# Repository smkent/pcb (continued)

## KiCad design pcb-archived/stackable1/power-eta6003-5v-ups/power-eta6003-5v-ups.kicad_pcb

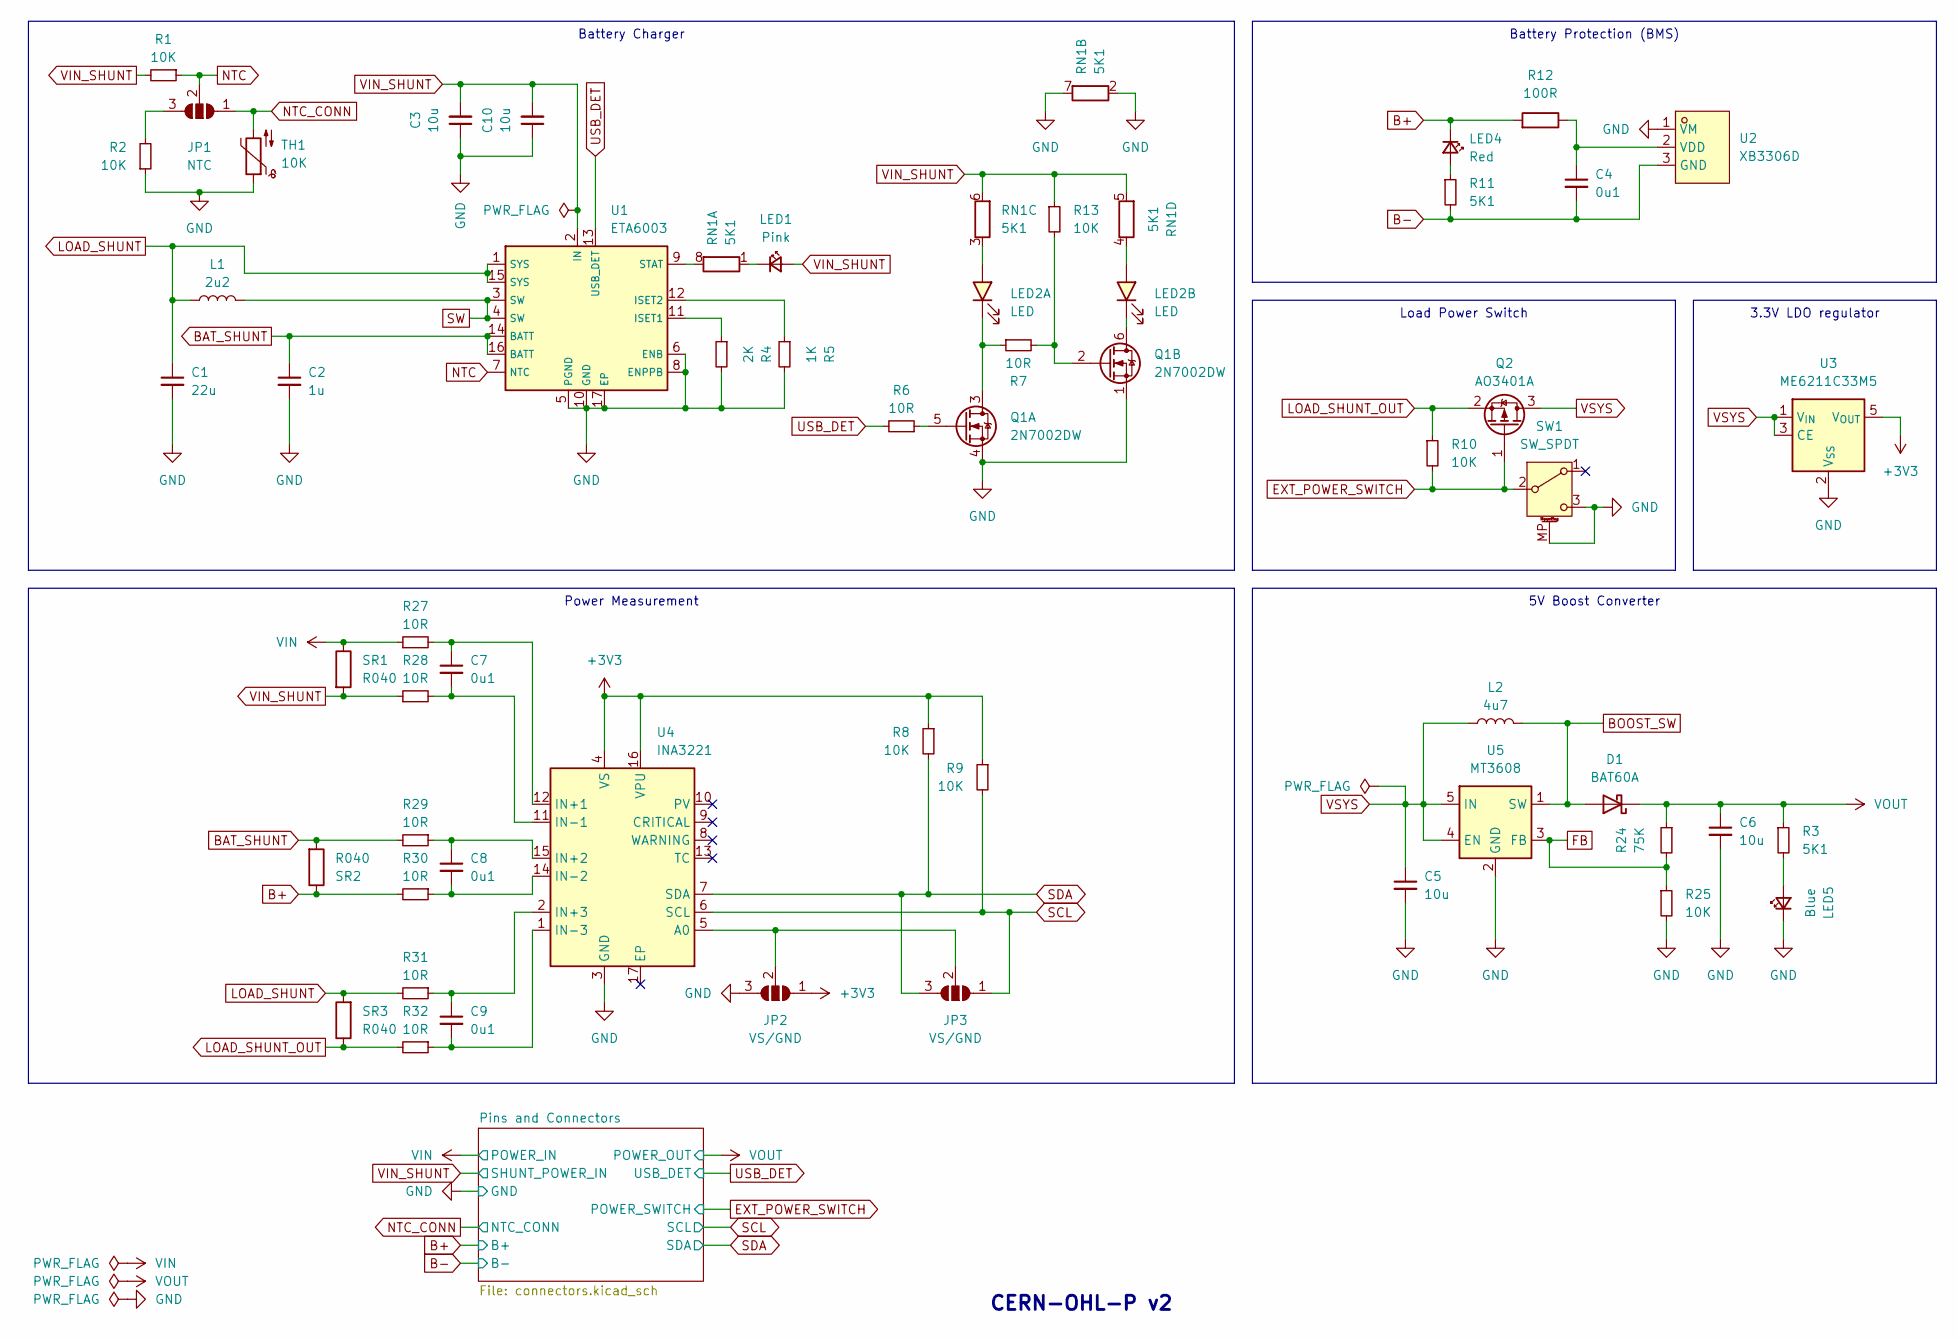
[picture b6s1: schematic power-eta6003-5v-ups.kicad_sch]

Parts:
C1: 22u; C_0805_2012Metric_Pad1.18x1.45mm_HandSolder; LCSC Part C45783
C2: 1u; C_0402_1005Metric_simple; LCSC Part C52923
C3: 10u; C_0805_2012Metric_Pad1.18x1.45mm_wide-center_HandSolder; LCSC Part C15850
C4, C7, C8, C9: 0u1; C_0402_1005Metric_simple; LCSC Part C1525
C5, C6: 10u; C_0603_1608Metric_Pad1.08x0.95mm_HandSolder; LCSC Part C19702
C10: 10u; C_0805_2012Metric_Pad1.18x1.45mm_HandSolder; LCSC Part C15850
D1: BAT60A; D_SOD-323_HandSoldering_simple; LCSC Part C7502695
JP1: NTC; SolderJumper-3_P1.3mm_Open_RoundedPad1.0x1.5mm
JP2, JP3: VS/GND; SolderJumper-3_P1.0mm_Open_RoundedPad_simple
L1: 2u2; L_1210_3225Metric_Pad1.42x2.65mm_HandSolder; LCSC Part C5832372
L2: 4u7; Inductor_Multi_7.0x6.6_1210; LCSC Part C5307631
LED1: Pink; LED_0603_1608Metric_Pad1.05x0.95mm_HandSolder_simple
LED2: LED; LED-ARRAY-SMD_4P-L2.0-W1.3-RD; LCSC Part C375547
LED4: Red; LED_0603_1608Metric_Pad1.05x0.95mm_HandSolder_simple; LCSC Part C2286
LED5: Blue; LED_0603_1608Metric_Pad1.05x0.95mm_HandSolder_simple
Q1: 2N7002DW; SOT-23-6_trimmed-pads_simple; LCSC Part C5190214
Q2: AO3401A; SOT-23_simple; LCSC Part C15127
R1, R2, R8, R9, R10, R13, R25: 10K; R_0402_1005Metric_simple; LCSC Part C25744
R3, R11: 5K1; R_0402_1005Metric_simple; LCSC Part C25905
R4: 2K; R_0603_1608Metric_Pad0.98x0.95mm_HandSolder; LCSC Part C22975
R5: 1K; R_0603_1608Metric_Pad0.98x0.95mm_HandSolder; LCSC Part C21190
R6, R7, R27, R28, R29, R30, R31, R32: 10R; R_0402_1005Metric_simple; LCSC Part C25077
R12: 100R; R_0402_1005Metric_simple; LCSC Part C25076
R24: 75K; R_0402_1005Metric_simple; LCSC Part C25798
RN1: 5K1; R_Array_Convex_4x0402; LCSC Part C2991336
SR1, SR2, SR3: R040; R_2512_6332Metric_Pad1.40x3.35mm_HandSolder; LCSC Part C2985725
SW1: SW_SPDT; SW-SMD_3P-P1.50_L2.7-W6.6; LCSC Part C319020
TH1: 10K; JST_SH_SM02B-SRSS-TB_1x02-1MP_P1.00mm_Horizontal
U1: ETA6003; ETA6003_QFN-16-1EP_3x3mm_P0.5mm_EP1.7x1.7mm_ThermalVias; LCSC Part C5455585
U2: XB3306D; SOT-23_simple; LCSC Part C2759992
U3: ME6211C33M5; SOT-23-5_simple; LCSC Part C82942
U4: INA3221; Texas_RGV0016A_VQFN-16-1EP_4x4mm_P0.65mm_EP2.1x2.1mm_Therma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; LCSC Part C181255
U5: MT3608; SOT-23-6_Handsoldering_simple; LCSC Part C84817

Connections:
+3V3: JP2.1 (A), R8.1, R9.1, U3.5 (V_{OUT}), U4.4 (VS), U4.16 (VPU)
B+: LED4.1 (K), R12.2, R30.2, SR2.1; also elsewhere on the board
B-: C4.2, R11.2, U2.3 (GND); also elsewhere on the board
BAT_SHUNT: C2.1, R29.2, SR2.2, U1.14 (BATT), U1.16 (BATT)
BOOST_SW: D1.2 (A), L2.2, U5.1 (SW)
EXT_POWER_SWITCH: Q2.1 (G), R10.2, SW1.2 (B); also elsewhere on the board
FB: R24.2, R25.1, U5.3 (FB)
GND: C1.2, C2.2, C3.1, C5.2, C6.2, C10.1, JP2.3 (B), LED5.1 (K), Q1.1 (S), Q1.4 (S), R2.1, R4.2, R5.2, R25.2, RN1.2 (R2.1), RN1.7 (R2.2), SW1.3 (C), SW1.MP (MountPin), TH1.1, U1.5 (PGND), U1.6 (ENB), U1.8 (ENPPB), U1.10 (GND), U1.17 (EP), U2.1 (VM), U3.2 (V_{SS}), U4.3 (GND), U5.2 (GND); also elsewhere on the board
LOAD_SHUNT: C1.1, L1.1, R31.2, SR3.2, U1.1 (SYS), U1.15 (SYS)
LOAD_SHUNT_OUT: Q2.2 (S), R10.1, R32.2, SR3.1
NTC: JP1.2 (C), R1.1, U1.7 (NTC)
NTC_CONN: JP1.1 (A), TH1.2; also elsewhere on the board
unnamed: JP1.3 (B), R2.2
unnamed: JP2.2 (C), JP3.2 (C), U4.5 (A0)
unnamed: LED1.1 (K), RN1.1 (R1.1)
unnamed: LED2.1 (RED_A), RN1.3 (R3.1)
unnamed: LED2.2 (RED_K), Q1.3 (D), R7.1
unnamed: LED2.3 (BLUE_A), RN1.4 (R4.1)
unnamed: LED2.4 (BLUE_K), Q1.6 (D)
unnamed: LED4.2 (A), R11.1
unnamed: LED5.2 (A), R3.2
unnamed: Q1.5 (G), R6.1
unnamed: Q1.2 (G), R7.2, R13.2
unnamed: RN1.8 (R1.2), U1.9 (STAT)
unnamed: R4.1, U1.11 (ISET1)
unnamed: R5.1, U1.12 (ISET2)
unnamed: C4.1, R12.1, U2.2 (VDD)
unnamed: C7.1, R27.2, U4.12 (IN+1)
unnamed: C8.1, R29.1, U4.15 (IN+2)
unnamed: C9.1, R31.1, U4.2 (IN+3)
unnamed: C7.2, R28.2, U4.11 (IN-1)
unnamed: C8.2, R30.1, U4.14 (IN-2)
unnamed: C9.2, R32.1, U4.1 (IN-3)
SCL: JP3.1 (A), R9.2, U4.6 (SCL); also elsewhere on the board
SDA: JP3.3 (B), R8.2, U4.7 (SDA); also elsewhere on the board
SW: L1.2, U1.3 (SW), U1.4 (SW)
USB_DET: R6.2, U1.13 (USB_DET); also elsewhere on the board
VIN: R27.1, SR1.1; also elsewhere on the board
VIN_SHUNT: C3.2, C10.2, LED1.2 (A), R1.2, R13.1, R28.1, RN1.5 (R4.2), RN1.6 (R3.2), SR1.2, U1.2 (IN); also elsewhere on the board
VOUT: C6.1, D1.1 (K), R3.1, R24.1; also elsewhere on the board
VSYS: C5.1, L2.1, Q2.3 (D), U3.1 (V_{IN}), U3.3 (CE), U5.4 (EN), U5.5 (IN)

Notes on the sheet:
3.3V LDO regulator
5V Boost Converter
Battery Protection (BMS)
Battery Charger
Power Measurement
Load Power Switch
CERN-OHL-P v2

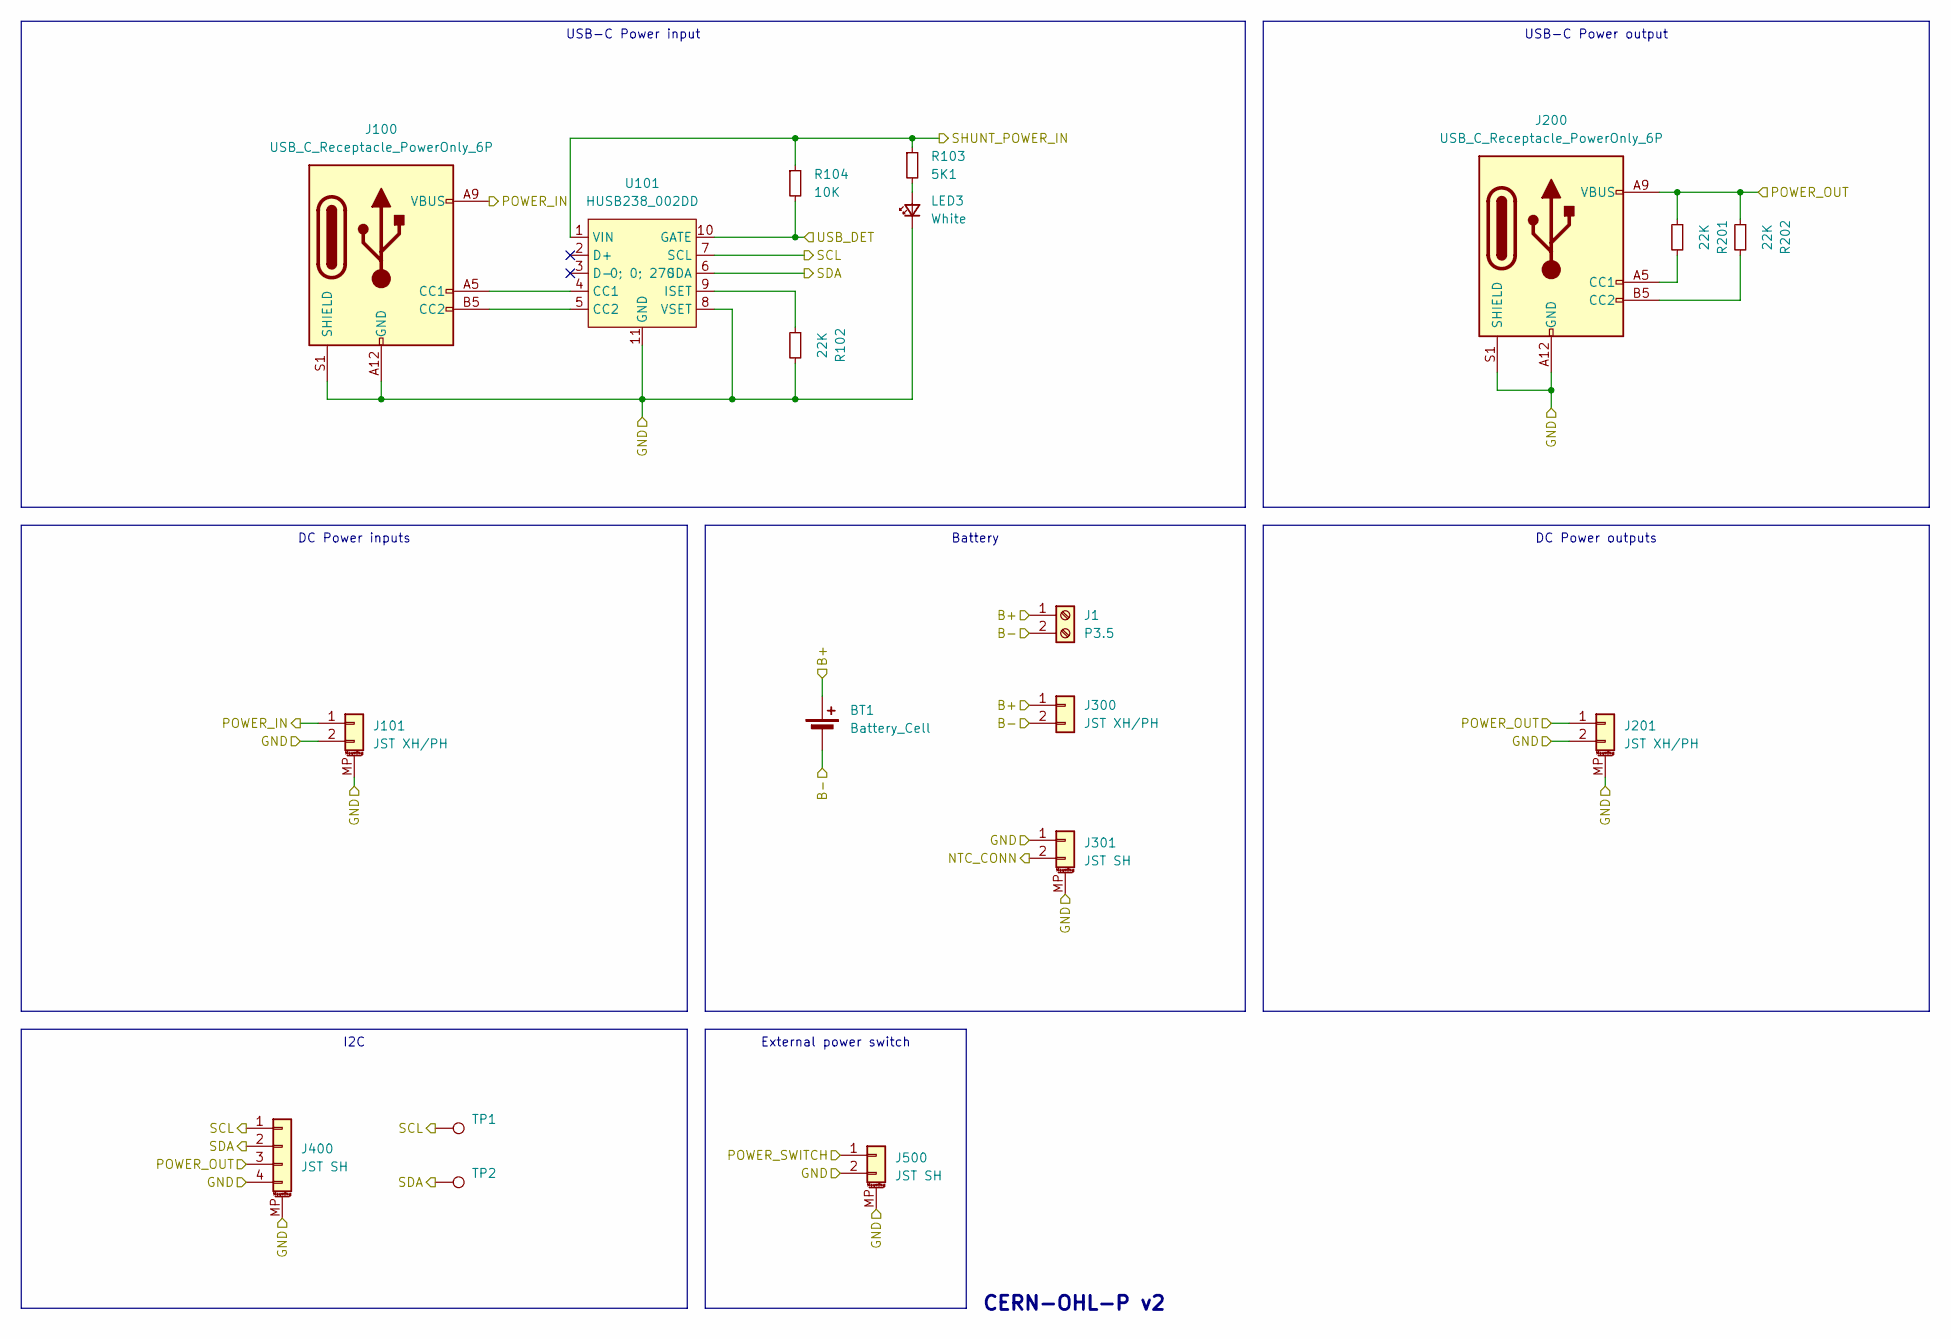
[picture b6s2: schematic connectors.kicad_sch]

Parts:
BT1: Battery_Cell; BAT-TH_18650-A5BJ001
J1: P3.5; TerminalBlock_Phoenix_PT-1,5-2-3.5-H_1x02_P3.50mm_Horizonta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
J100, J200: USB_C_Receptacle_PowerOnly_6P; USB_C_Receptacle_GCT_USB4125-xx-x_6P_TopMnt_Horizontal_hand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; LCSC Part C2927029
J101, J201: JST XH/PH; Conn_Combo_JST-1x02-XH_PH-SMD-alt-pad2gnd
J300: JST XH/PH; Conn_Combo_JST-1x02-XH_PH-THT-pad2gnd
J301, J500: JST SH; JST_SH_SM02B-SRSS-TB_1x02-1MP_P1.00mm_Horizontal; LCSC Part C7433423
J400: JST SH; JST_SH_SM04B-SRSS-TB_1x04-1MP_P1.00mm_Horizontal; LCSC Part C7433425
LED3: White; LED_0603_1608Metric_Pad1.05x0.95mm_HandSolder_simple
R102, R201, R202: 22K; R_0603_1608Metric_Pad0.98x0.95mm_HandSolder; LCSC Part C31850
R103: 5K1; R_0402_1005Metric_simple; LCSC Part C25905
R104: 10K; R_0402_1005Metric_simple; LCSC Part C25744
TP1, TP2: TestPoint_Pad_D1.5mm
U101: HUSB238_002DD; WDFN-10-1EP_3x3mm_P0.5mm_EP1.8x2.5mm_ThermalVias_half; LCSC Part C7471904

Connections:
B+: BT1.1 (+), J1.1, J300.1; also elsewhere on the board
B-: BT1.2 (-), J1.2, J300.2; also elsewhere on the board
EXT_POWER_SWITCH: J500.1; also elsewhere on the board
GND: J100.A12 (GND), J100.B12 (GND), J100.S1 (SHIELD), J101.2, J101.MP (MountPin), J200.A12 (GND), J200.B12 (GND), J200.S1 (SHIELD), J201.2, J201.MP (MountPin), J301.1, J301.MP (MountPin), J400.4, J400.MP (MountPin), J500.2, J500.MP (MountPin), LED3.1 (K), R102.2, U101.8 (VSET), U101.11 (GND); also elsewhere on the board
NTC_CONN: J301.2; also elsewhere on the board
unnamed: J100.A5 (CC1), U101.4 (CC1)
unnamed: J100.B5 (CC2), U101.5 (CC2)
unnamed: J200.A5 (CC1), R201.2
unnamed: J200.B5 (CC2), R202.2
unnamed: LED3.2 (A), R103.2
unnamed: R102.1, U101.9 (ISET)
SCL: J400.1, TP1.1, U101.7 (SCL); also elsewhere on the board
SDA: J400.2, TP2.1, U101.6 (SDA); also elsewhere on the board
USB_DET: R104.2, U101.10 (GATE); also elsewhere on the board
VIN: J100.A9 (VBUS), J100.B9 (VBUS), J101.1; also elsewhere on the board
VIN_SHUNT: R103.1, R104.1, U101.1 (VIN); also elsewhere on the board
VOUT: J200.A9 (VBUS), J200.B9 (VBUS), J201.1, J400.3, R201.1, R202.1; also elsewhere on the board

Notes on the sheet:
DC Power outputs
USB-C Power output
DC Power inputs
I2C
USB-C Power input
Battery
External power switch
CERN-OHL-P v2

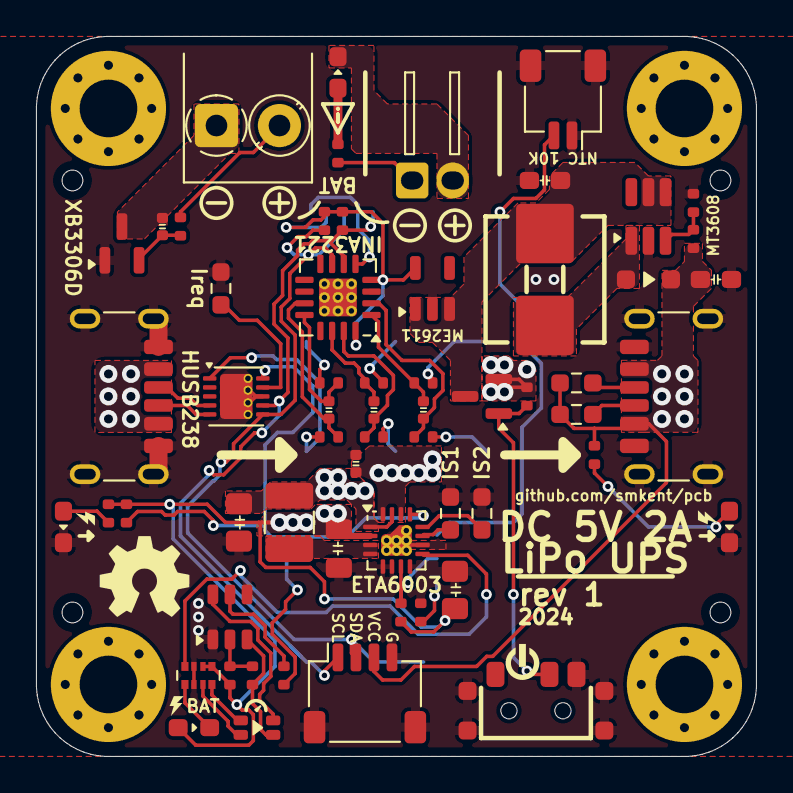
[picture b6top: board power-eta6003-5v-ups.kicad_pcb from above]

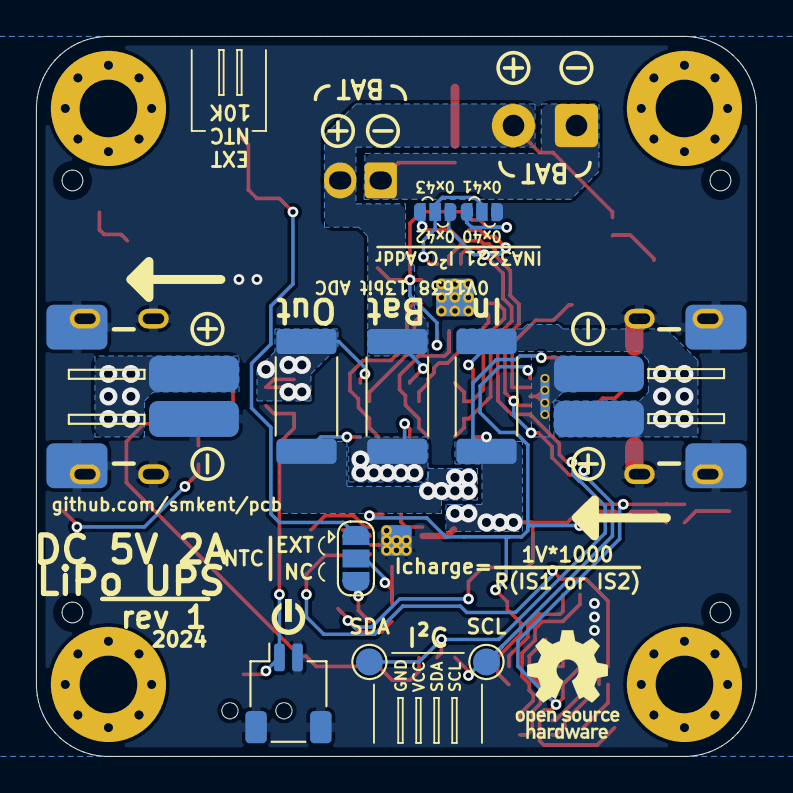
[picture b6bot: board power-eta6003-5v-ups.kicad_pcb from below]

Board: 2 copper layers, 40.0 x 40.0 mm, 71 parts (11 on the bottom side), 47 nets.

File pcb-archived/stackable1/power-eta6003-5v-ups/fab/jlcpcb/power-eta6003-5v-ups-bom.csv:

Comment,Designator,Footprint,LCSC
SW_SPDT,SW1,lcsc:SW-SMD_3P-P1.50_L2.7-W6.6,C319020
2u2,L1,Inductor_SMD:L_1210_3225Metric_Pad1.42x2.65mm_HandSolder,C5832372
10K,"R1,R2,R8,R9,R10,R13,R25,R104",custom:R_0402_1005Metric_simple,C25744
Pink,LED1,custom:LED_0603_1608Metric_Pad1.05x0.95mm_HandSolder_simple,
Red,LED4,custom:LED_0603_1608Metric_Pad1.05x0.95mm_HandSolder_simple,C2286
0u1,"C4,C7,C8,C9",custom:C_0402_1005Metric_simple,C1525
10R,"R6,R7,R27,R28,R29,R30,R31,R32",custom:R_0402_1005Metric_simple,C25077
10u,"C5,C6",custom:C_0603_1608Metric_Pad1.08x0.95mm_HandSolder,C19702
5K1,"R3,R11,R103",custom:R_0402_1005Metric_simple,C25905
100R,R12,custom:R_0402_1005Metric_simple,C25076
R040,"SR1,SR2,SR3",Resistor_SMD:R_2512_6332Metric_Pad1.40x3.35mm_HandSolder,C2985725
2N7002DW,Q1,custom:SOT-23-6_trimmed-pads_simple,C5190214
75K,R24,custom:R_0402_1005Metric_simple,C25798
1u,C2,custom:C_0402_1005Metric_simple,C52923
10u,C10,custom:C_0805_2012Metric_Pad1.18x1.45mm_HandSolder,C15850
5K1,RN1,Resistor_SMD:R_Array_Convex_4x0402,C2991336
ME6211C33M5,U3,custom:SOT-23-5_simple,C82942
AO3401A,Q2,custom:SOT-23_simple,C15127
10u,C3,custom:C_0805_2012Metric_Pad1.18x1.45mm_wide-center_HandSolder,C15850
1K,R5,Resistor_SMD:R_0603_1608Metric_Pad0.98x0.95mm_HandSolder, C21190
INA3221,U4,custom:Texas_RGV0016A_VQFN-16-1EP_4x4mm_P0.65mm_EP2.1x2.1mm_ThermalVias,C181255
22u,C1,custom:C_0805_2012Metric_Pad1.18x1.45mm_HandSolder,C45783
XB3306D,U2,custom:SOT-23_simple,C2759992
BAT60A,D1,custom:D_SOD-323_HandSoldering_simple,C7502695
ETA6003,U1,custom:ETA6003_QFN-16-1EP_3x3mm_P0.5mm_EP1.7x1.7mm_ThermalVias,C5455585
2K,R4,Resistor_SMD:R_0603_1608Metric_Pad0.98x0.95mm_HandSolder, C22975
MT3608,U5,custom:SOT-23-6_Handsoldering_simple,C84817
LED,LED2,lcsc:LED-ARRAY-SMD_4P-L2.0-W1.3-RD,C375547
Blue,LED5,custom:LED_0603_1608Metric_Pad1.05x0.95mm_HandSolder_simple,
4u7,L2,custom:Inductor_Multi_7.0x6.6_1210,C5307631
JST XH/PH,J300,custom:Conn_Combo_JST-1x02-XH_PH-THT-pad2gnd,
USB_C_Receptacle_PowerOnly_6P,"J100,J200",custom:USB_C_Receptacle_GCT_USB4125-xx-x_6P_TopMnt_Horizontal_handsolder,C2927029
JST XH/PH,"J101,J201",custom:Conn_Combo_JST-1x02-XH_PH-SMD-alt-pad2gnd,
P3.5,J1,"custom:TerminalBlock_Phoenix_PT-1,5-2-3.5-H_1x02_P3.50mm_Horizontal_custom_pad2gnd",
HUSB238_002DD,U101,custom:WDFN-10-1EP_3x3mm_P0.5mm_EP1.8x2.5mm_ThermalVias_half,C7471904
22K,"R102,R201,R202",Resistor_SMD:R_0603_1608Metric_Pad0.98x0.95mm_HandSolder,C31850
JST SH,"J301,J500",connectors:JST_SH_SM02B-SRSS-TB_1x02-1MP_P1.00mm_Horizontal,C7433423
JST SH,J400,connectors:JST_SH_SM04B-SRSS-TB_1x04-1MP_P1.00mm_Horizontal,C7433425
White,LED3,custom:LED_0603_1608Metric_Pad1.05x0.95mm_HandSolder_simple,

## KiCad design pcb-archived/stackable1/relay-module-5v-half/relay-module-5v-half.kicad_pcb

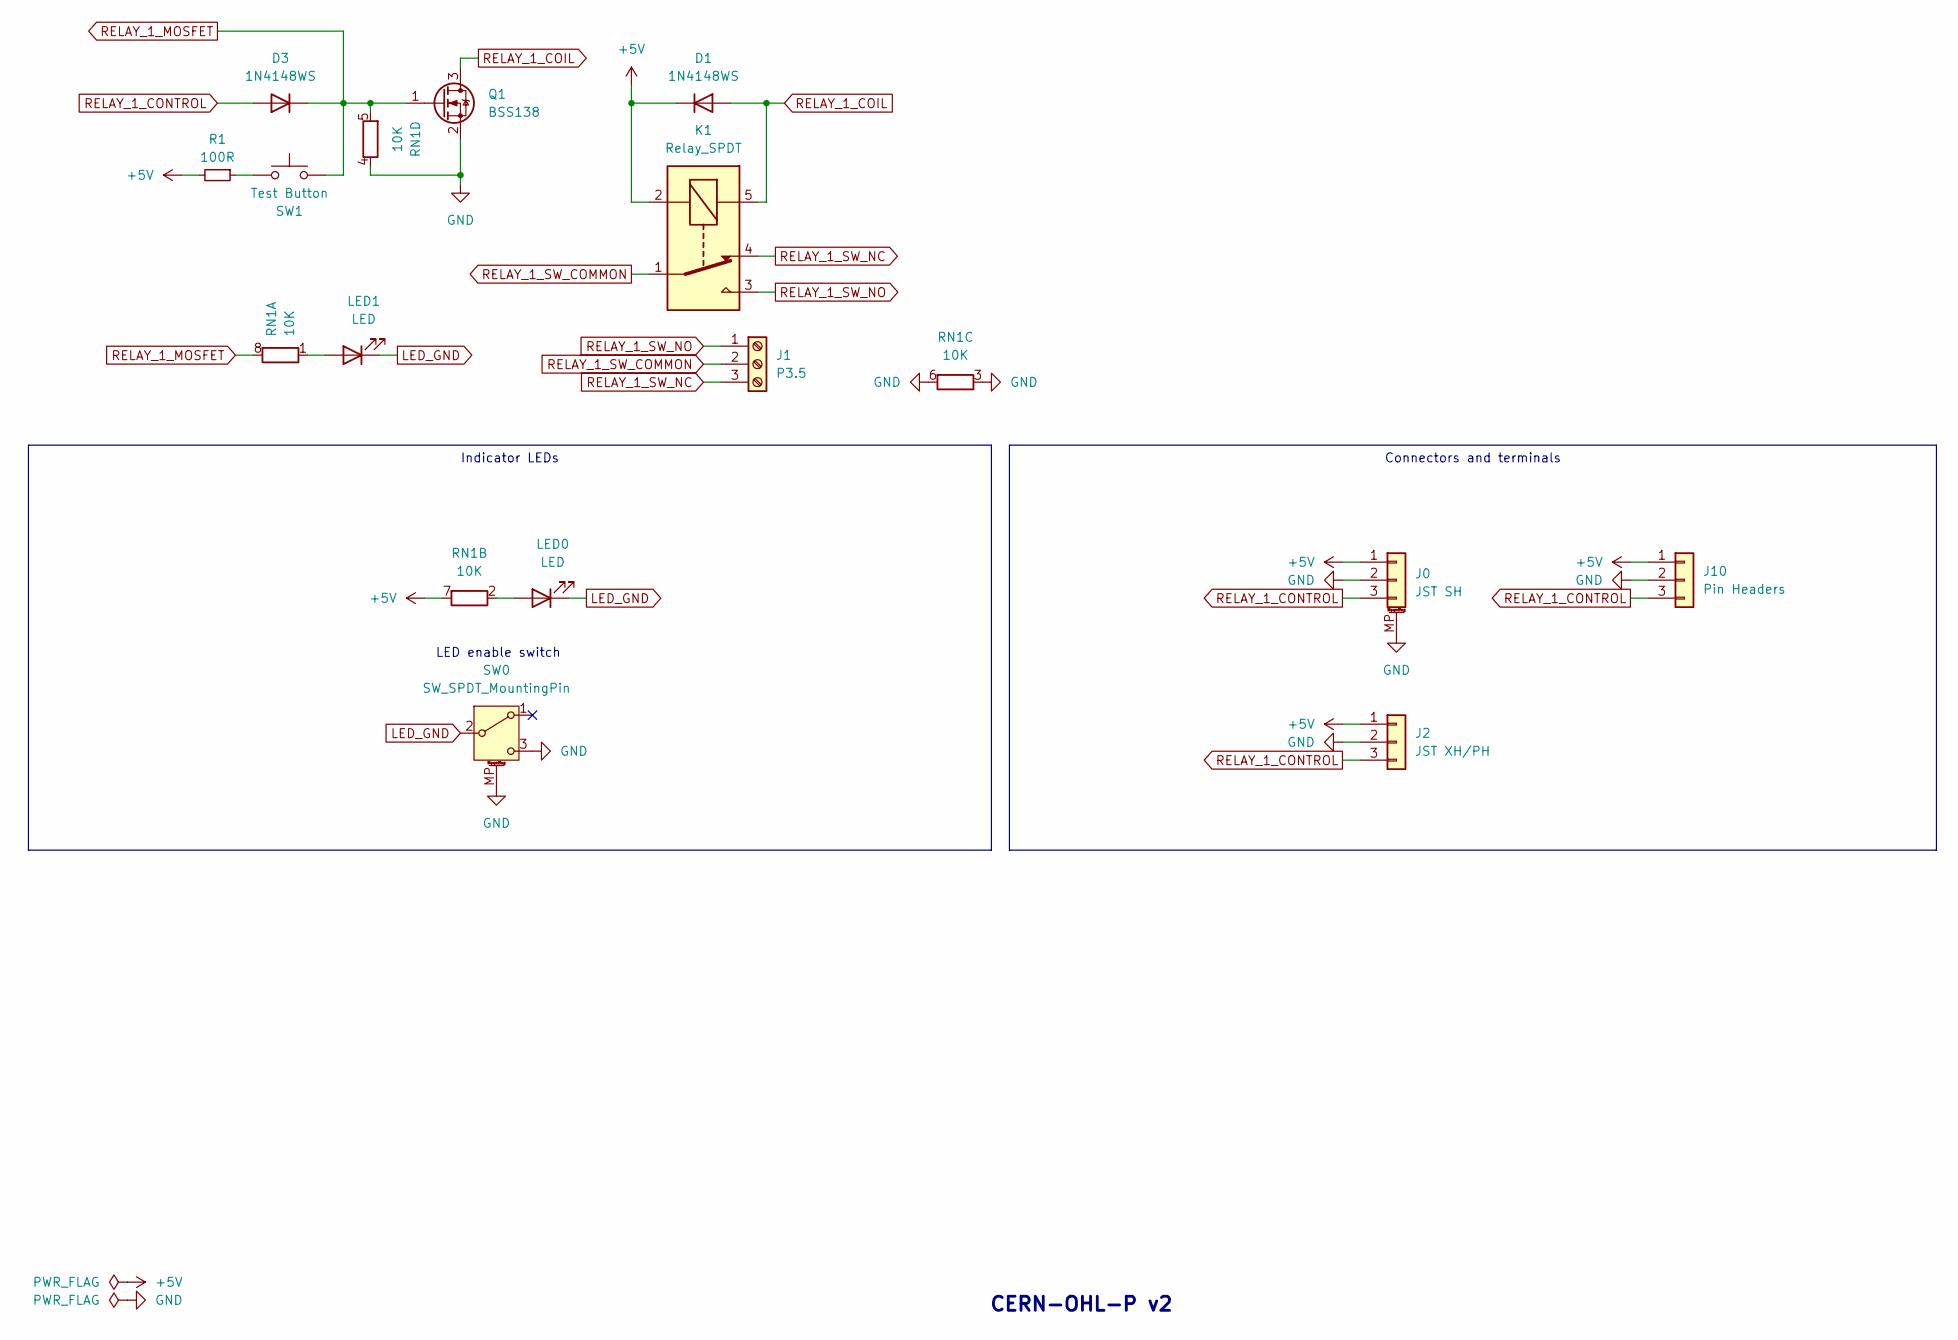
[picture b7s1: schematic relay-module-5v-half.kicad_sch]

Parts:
D1, D3: 1N4148WS; D_SOD-323_HandSoldering_simple
J0: JST SH; JST_SH_SM03B-SRSS-TB_1x03-1MP_P1.00mm_Horizontal
J1: P3.5; Conn_Combo_TerminalBlock_P3.5_JST-XH_PH_1x03
J2: JST XH/PH; Conn_Combo_JST-1x03-XH_PH-THT_pad2gnd
J10: Pin Headers; PinHeader_1x03_P2.54mm_Vertical_simple_pad2gnd
K1: Relay_SPDT; Relay_SPDT_SANYOU_SRD_Series_Form_C
LED0, LED1: LED; LED_0805_2012Metric_Pad1.15x1.40mm_HandSolder_simple
Q1: BSS138; SOT-23_simple
R1: 100R; R_0805_2012Metric_Pad1.20x1.40mm_HandSolder
RN1: 10K; R_Array_Convex_4x0603
SW0: SW_SPDT_MountingPin; SW-SMD_3P-P1.50_L2.7-W6.6
SW1: Test Button; SW-SMD_BZCN_TSA002A35XXX

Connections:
+5V: D1.1 (K), J0.1, J2.1, J10.1, K1.2, R1.2, RN1.7 (R2.2)
GND: J0.2, J0.MP (MountPin), J2.2, J10.2, Q1.2 (S), RN1.3 (R3.1), RN1.4 (R4.1), RN1.6 (R3.2), SW0.3 (C), SW0.MP (MountPin)
LED_GND: LED0.1 (K), LED1.1 (K), SW0.2 (B)
unnamed: LED0.2 (A), RN1.2 (R2.1)
unnamed: LED1.2 (A), RN1.1 (R1.1)
unnamed: R1.1, SW1.2
RELAY_1_COIL: D1.2 (A), K1.5, Q1.3 (D)
RELAY_1_CONTROL: D3.2 (A), J0.3, J2.3, J10.3
RELAY_1_MOSFET: D3.1 (K), Q1.1 (G), RN1.5 (R4.2), RN1.8 (R1.2), SW1.1
RELAY_1_SW_COMMON: J1.2, K1.1
RELAY_1_SW_NC: J1.3, K1.4
RELAY_1_SW_NO: J1.1, K1.3

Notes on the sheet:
Indicator LEDs
Connectors and terminals
CERN-OHL-P v2
LED enable switch

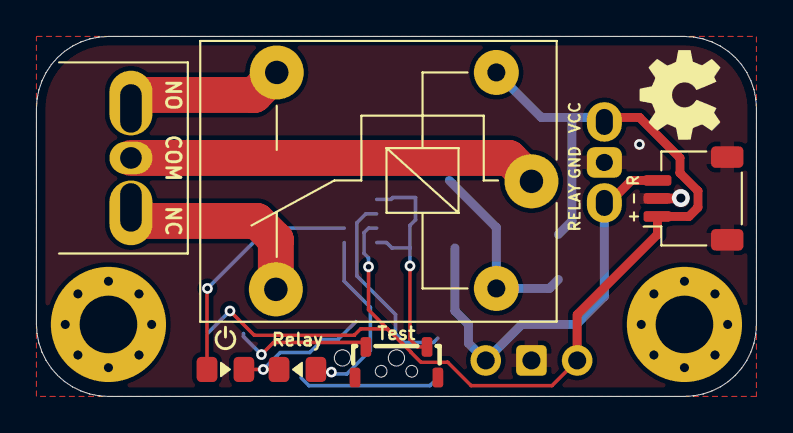
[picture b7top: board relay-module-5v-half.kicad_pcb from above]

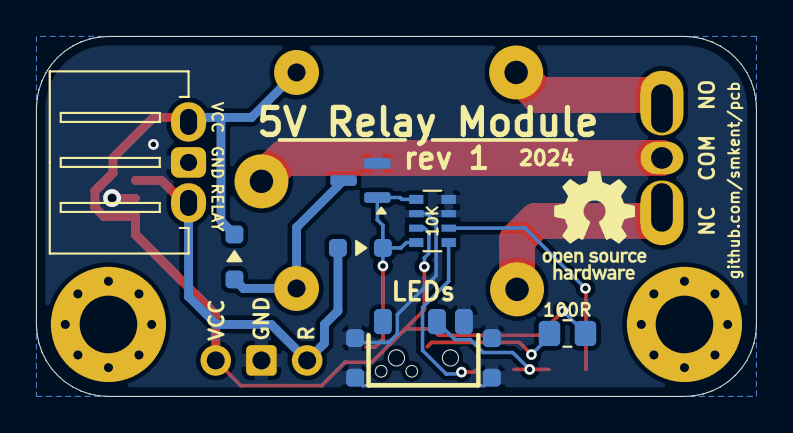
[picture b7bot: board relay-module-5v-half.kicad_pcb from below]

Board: 2 copper layers, 40.0 x 20.0 mm, 14 parts (7 on the bottom side), 12 nets.
